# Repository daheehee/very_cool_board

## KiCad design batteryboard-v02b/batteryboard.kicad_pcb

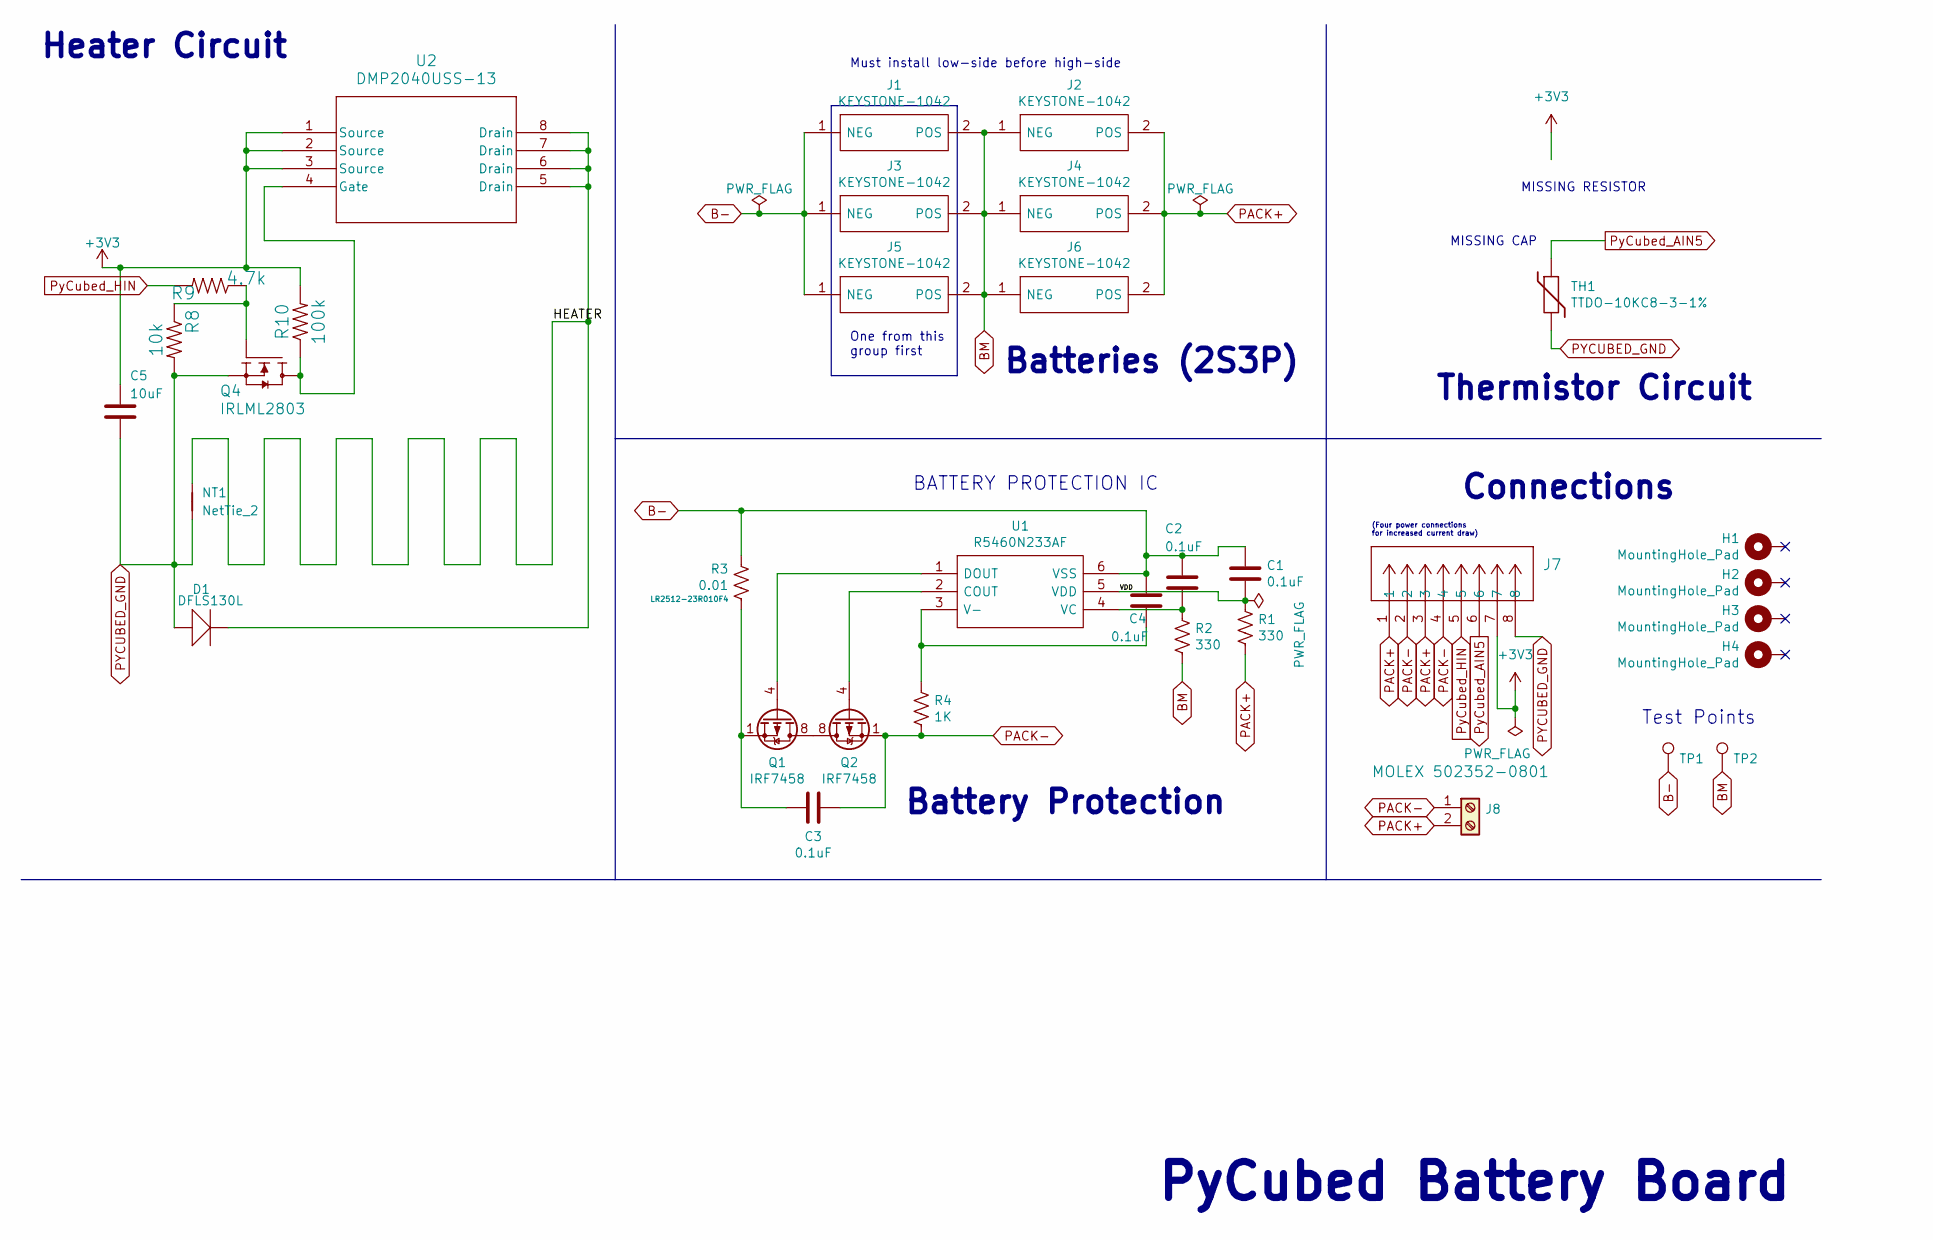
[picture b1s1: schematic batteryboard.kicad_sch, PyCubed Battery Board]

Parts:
C1, C2, C3, C4: 0.1uF; C_0603_1608Metric
C5: 10uF; C_0603_1608Metric
D1: DFLS130L; PWRDI-123
H1, H2, H3, H4: MountingHole_Pad; MountingHole_3.2mm_M3_DIN965_PadMOD
J1, J2, J3, J4, J5, J6: KEYSTONE-1042; Keystone_1042; Manufacturer_Part_Number 1042; Mouser Part Number 534-1042
J7: MOLEX 502352-0801; CONN_502352-0801_MOL
J8: Screw_Terminal_01x02; pheonix_2pos_screwterminal
NT1: NetTie_2; NetTie-2_SMD_Pad0.5mm
Q1, Q2: IRF7458; SOIC-8_3.9x4.9mm_P1.27mm
Q4: IRLML2803; SOT-23; Manufacturer_Part_Number MMBT2222AT
R1, R2: 330; R_0603_1608Metric
R3: 0.01; R_2512_6332Metric
R4: 1K; R_0603_1608Metric; Manufacturer_Part_Number LR2512-23R010F4
R8: 10k; R_0603_1608Metric
R9: 4.7k; R_0603_1608Metric
R10: 100k; R_0603_1608Metric
TH1: TTDO-10KC8-3-1%; R_Axial_DIN0204_L3.6mm_D1.6mm_P5.08mm_Horizontal
TP1, TP2: TestPoint; TestPoint_Loop_D1.80mm_Drill1.0mm_Beaded
U1: R5460N233AF; SOT-23-6; Manufacturer_Part_Number R5460N233AF-TR-FE; Mouser Part Number 848-R5460N233AFTRFE
U2: DMP2040USS-13; SOIC_2LSS-13_DIO

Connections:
+3V3: C5.1, J7.7, R10.2, U2.1 (Source), U2.2 (Source), U2.3 (Source)
/HEATER: D1.C, NT1.2, U2.5 (Drain), U2.6 (Drain), U2.7 (Drain), U2.8 (Drain)
/VDD: C1.2, R1.2, U1.5 (VDD)
B-: C1.1, C2.1, C4.1, J1.1 (NEG), J3.1 (NEG), J5.1 (NEG), R3.1, TP1.1, U1.6 (VSS)
BM: J1.2 (POS), J2.1 (NEG), J3.2 (POS), J4.1 (NEG), J5.2 (POS), J6.1 (NEG), R2.1, TP2.1
unnamed: C3.1, Q1.1 (S), Q1.2 (S), Q1.3 (S), R3.2
unnamed: Q1.5 (D), Q1.6 (D), Q1.7 (D), Q1.8 (D), Q2.5 (D), Q2.6 (D), Q2.7 (D), Q2.8 (D)
unnamed: Q1.4 (G), U1.1 (DOUT)
unnamed: Q2.4 (G), U1.2 (COUT)
unnamed: Q4.3 (D), R10.1, U2.4 (Gate)
unnamed: Q4.1 (G), R8.1, R9.1
unnamed: C4.2, R4.1, U1.3 (V-)
unnamed: C2.2, R2.2, U1.4 (VC)
PACK+: J2.2 (POS), J4.2 (POS), J6.2 (POS), J7.1, J7.3, J8.2, R1.1
PACK-: C3.2, J7.2, J7.4, J8.1, Q2.1 (S), Q2.2 (S), Q2.3 (S), R4.2
PYCUBED_GND: C5.2, D1.A, J7.8, NT1.1, Q4.2 (S), R8.2, TH1.2
PyCubed_AIN5: J7.6, TH1.1
PyCubed_HIN: J7.5, R9.2

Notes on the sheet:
Connections
MISSING RESISTOR
(Four power connections for increased current draw)
One from this group first
PyCubed Battery Board
Batteries (2S3P)
Heater Circuit
Test Points
Battery Protection
MISSING CAP
Must install low-side before high-side
Thermistor Circuit
BATTERY PROTECTION IC

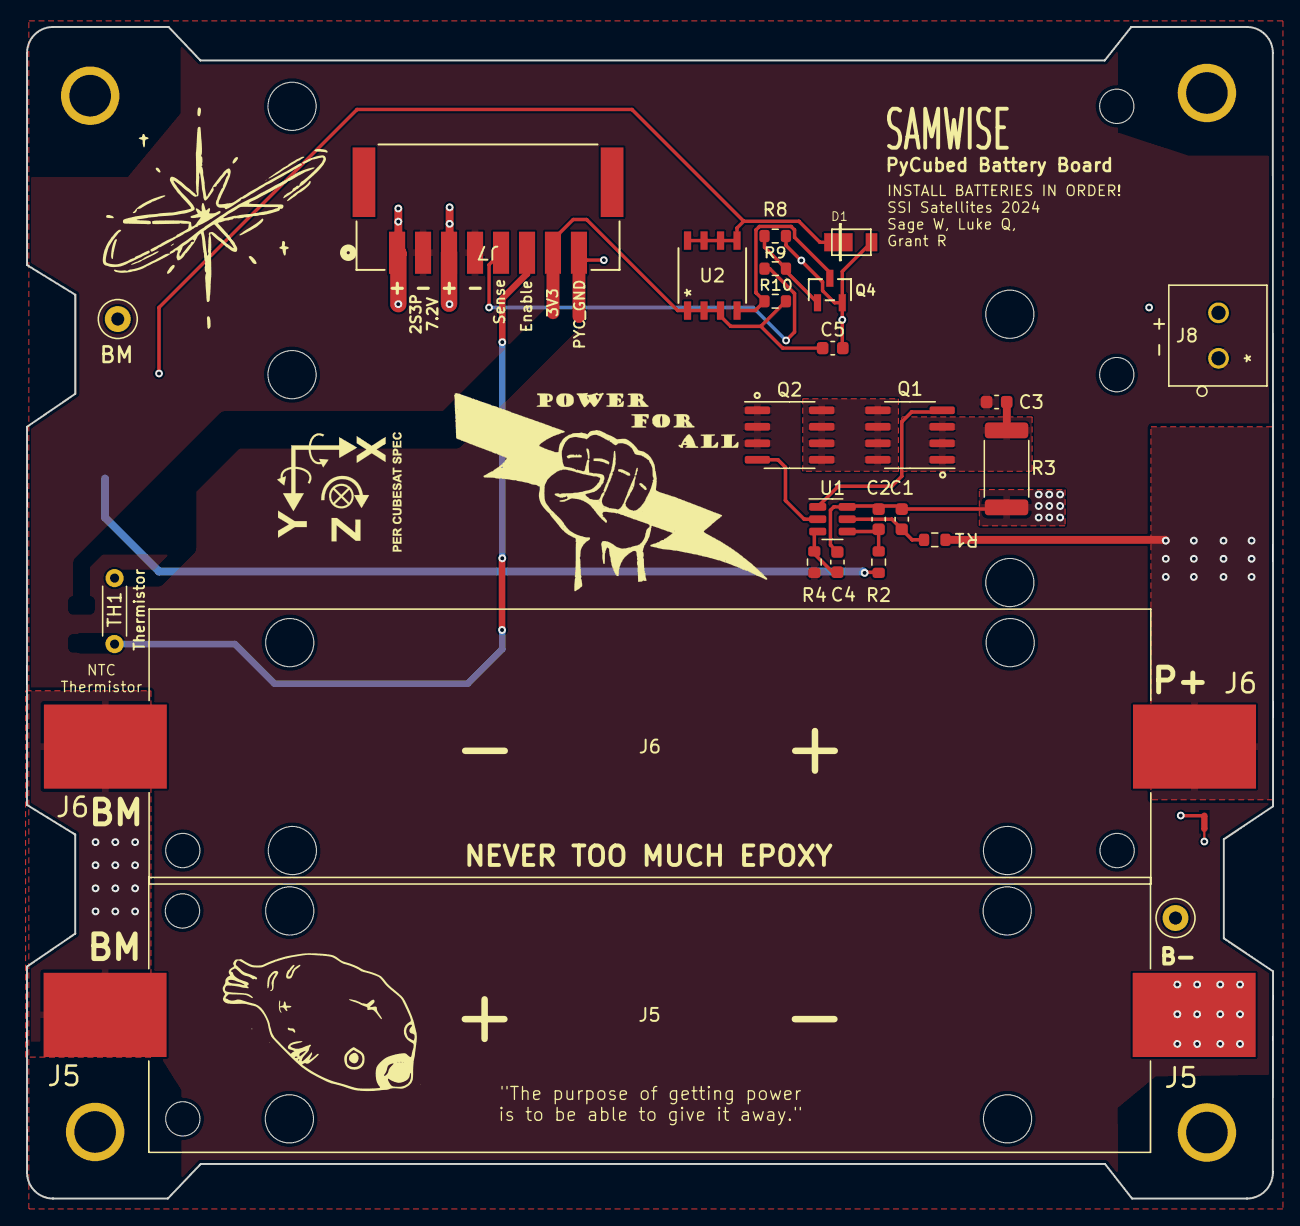
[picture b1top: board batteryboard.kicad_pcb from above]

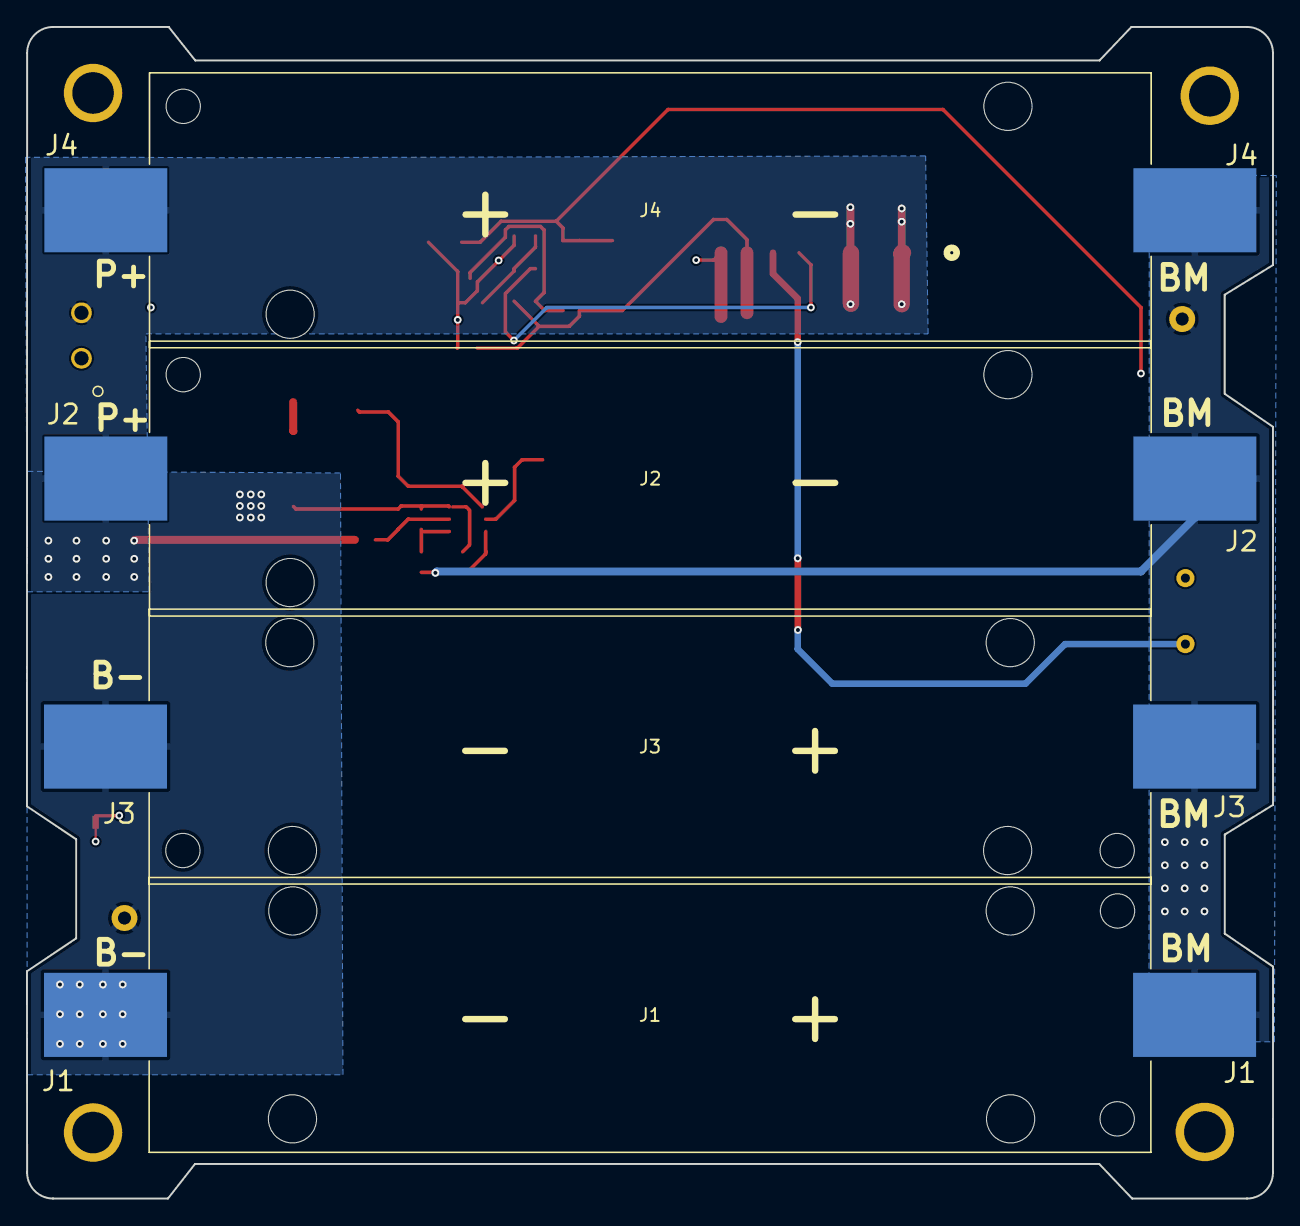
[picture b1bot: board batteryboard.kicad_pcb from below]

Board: 4 copper layers, 95.9 x 90.2 mm, 36 parts (5 on the bottom side), 18 nets.

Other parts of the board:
Ref**: Val**; PowerLogo
Ref**#2: Val**; XYZ_cubesat-bot

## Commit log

2024-09-29 image
2024-10-05 dont ask

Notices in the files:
parts and their libraries:
Copyright 2021 Accelerated Designs. All rights reserved.
